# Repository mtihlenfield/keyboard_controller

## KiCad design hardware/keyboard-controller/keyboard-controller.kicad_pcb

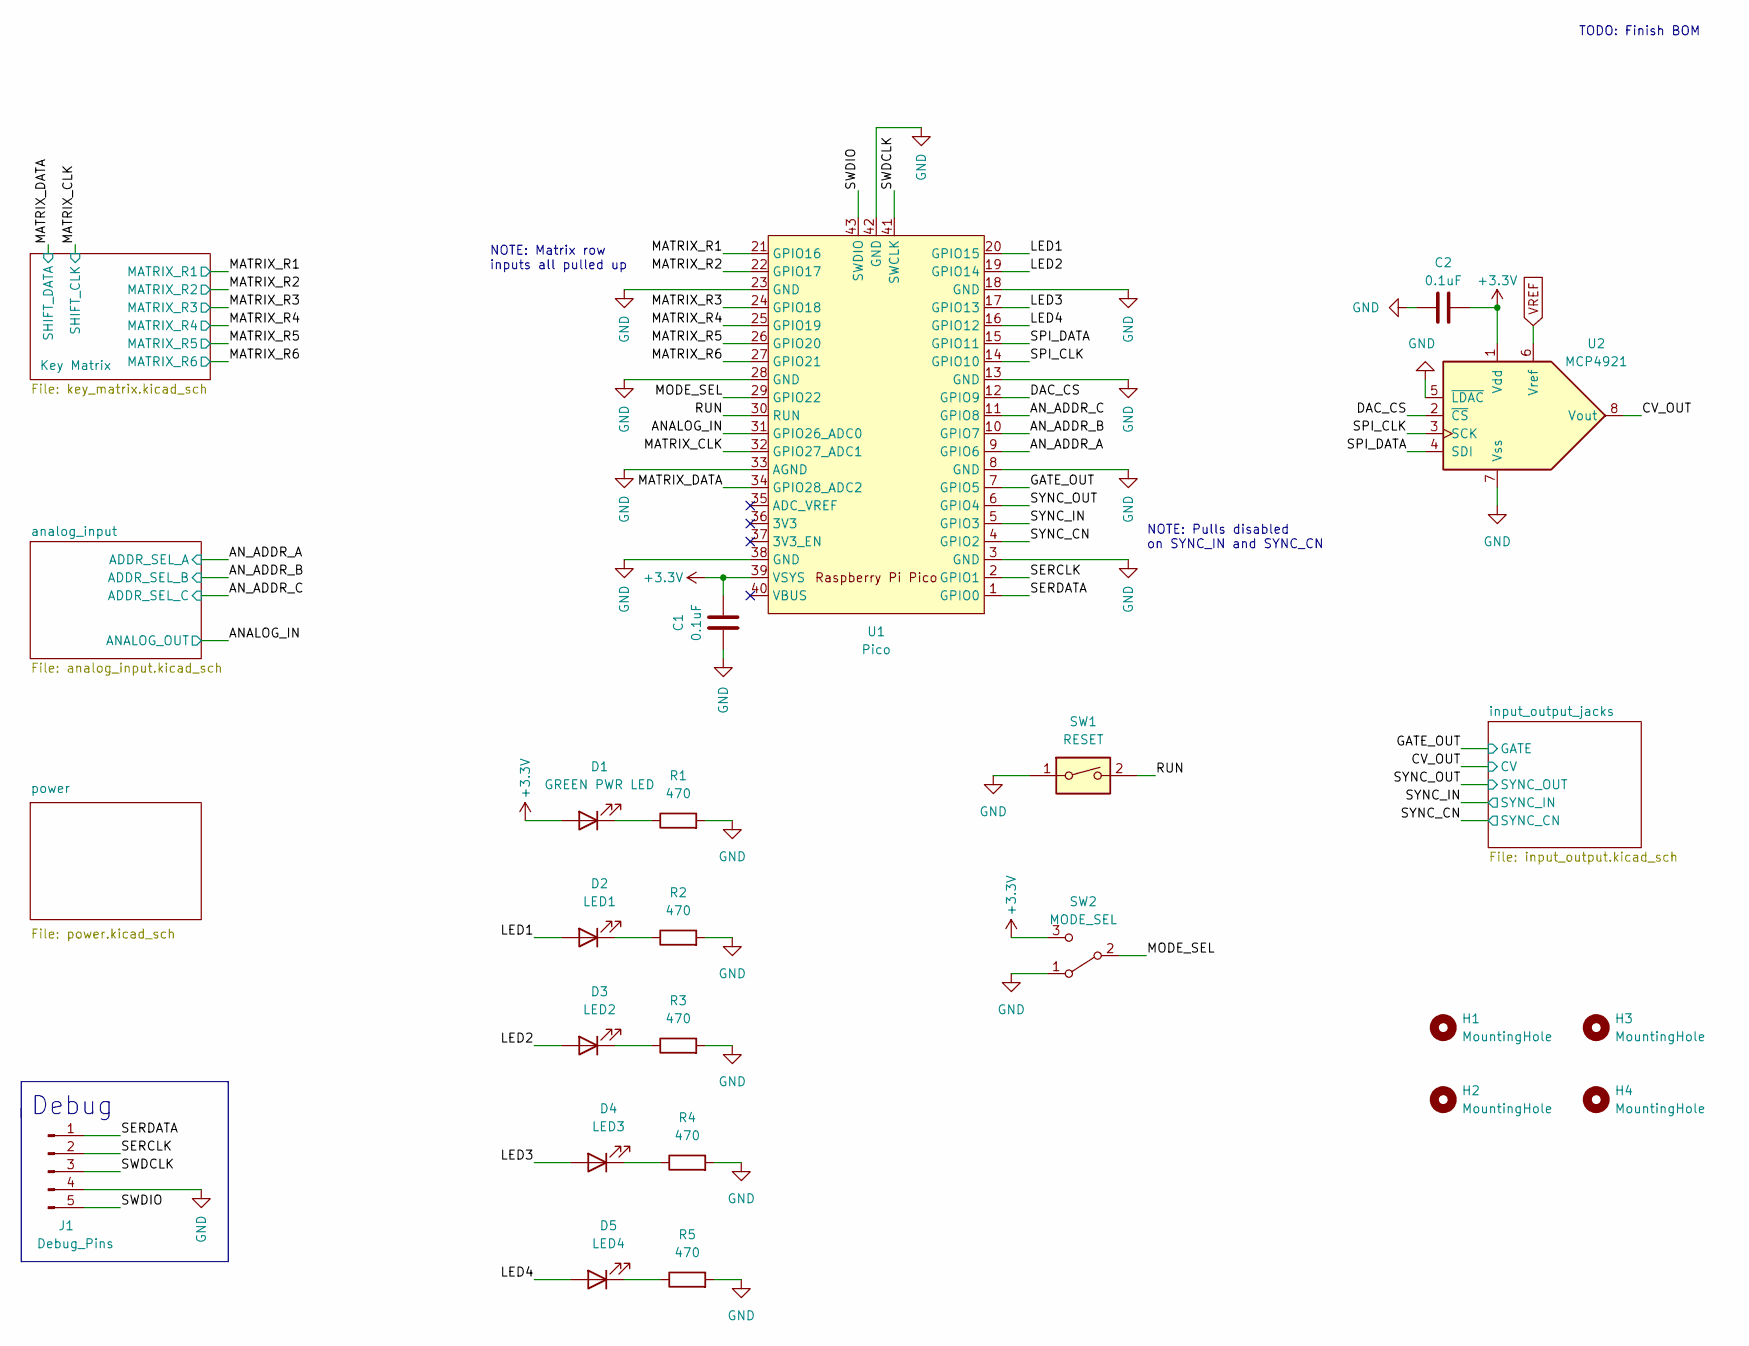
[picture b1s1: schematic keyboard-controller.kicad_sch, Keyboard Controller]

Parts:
C1, C2: 0.1uF; C_Disc_D5.0mm_W2.5mm_P3.0mm; Manufacturer Part No. 0.1uF 50V Ceramic Disc Capacitor
D1: GREEN PWR LED; LED_D5.0mm; Manufacturer Part No. LED 5mm Green
D2: LED1; LED_D5.0mm; Manufacturer Part No. C503B-RAN-CZ0C0AA1
D3: LED2; LED_D5.0mm; Manufacturer Part No. C503B-RAN-CZ0C0AA1
D4: LED3; LED_D5.0mm; Manufacturer Part No. C503B-RAN-CZ0C0AA1
D5: LED4; LED_D5.0mm; Manufacturer Part No. C503B-RAN-CZ0C0AA1
H1, H2, H3, H4: MountingHole; MountingHole_3.2mm_M3; Manufacturer Part No. N/A
J1: Debug_Pins; PinHeader_1x05_P2.54mm_Vertical; Manufacturer Part No. PHSS05G10
R1, R2, R3, R4, R5: 470; R_Axial_DIN0207_L6.8mm_D2.5mm_P10.16mm_Horizontal
SW1: RESET; SW_PUSH_6mm; Manufacturer Part No. Tact Switch 6x6mm 5mm
SW2: MODE_SEL; Slide_Switch_SPDT_SS12F44G5; Manufacturer Part No. SS12F44G5
U1: Pico; RPi_Pico_SMD_TH
U2: MCP4921; DIP-8_W7.62mm_Socket

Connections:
+3.3V: C1.2, C2.2, D1.2 (A), SW2.3 (C), U1.39 (VSYS), U2.1 (Vdd); also elsewhere on the board
/ANALOG_IN: U1.31 (GPIO26_ADC0); also elsewhere on the board
/AN_ADDR_A: U1.9 (GPIO6); also elsewhere on the board
/AN_ADDR_B: U1.10 (GPIO7); also elsewhere on the board
/AN_ADDR_C: U1.11 (GPIO8); also elsewhere on the board
/CV_OUT: U2.8 (Vout); also elsewhere on the board
/DAC_CS: U1.12 (GPIO9), U2.2 (~CS)
/GATE_OUT: U1.7 (GPIO5); also elsewhere on the board
/LED1: D2.2 (A), U1.20 (GPIO15)
/LED2: D3.2 (A), U1.19 (GPIO14)
/LED3: D4.2 (A), U1.17 (GPIO13)
/LED4: D5.2 (A), U1.16 (GPIO12)
/MATRIX_CLK: U1.32 (GPIO27_ADC1); also elsewhere on the board
/MATRIX_DATA: U1.34 (GPIO28_ADC2); also elsewhere on the board
/MATRIX_R1: U1.21 (GPIO16); also elsewhere on the board
/MATRIX_R2: U1.22 (GPIO17); also elsewhere on the board
/MATRIX_R3: U1.24 (GPIO18); also elsewhere on the board
/MATRIX_R4: U1.25 (GPIO19); also elsewhere on the board
/MATRIX_R5: U1.26 (GPIO20); also elsewhere on the board
/MATRIX_R6: U1.27 (GPIO21); also elsewhere on the board
/MODE_SEL: SW2.2 (B), U1.29 (GPIO22)
/RUN: SW1.2, U1.30 (RUN)
/SERCLK: J1.2, U1.2 (GPIO1)
/SERDATA: J1.1, U1.1 (GPIO0)
/SPI_CLK: U1.14 (GPIO10), U2.3 (SCK)
/SPI_DATA: U1.15 (GPIO11), U2.4 (SDI)
/SWDCLK: J1.3, U1.41 (SWCLK)
/SWDIO: J1.5, U1.43 (SWDIO)
/SYNC_CN: U1.4 (GPIO2); also elsewhere on the board
/SYNC_IN: U1.5 (GPIO3); also elsewhere on the board
/SYNC_OUT: U1.6 (GPIO4); also elsewhere on the board
GND: C1.1, C2.1, J1.4, R1.2, R2.2, R3.2, R4.2, R5.2, SW1.1, SW2.1 (A), U1.3 (GND), U1.8 (GND), U1.13 (GND), U1.18 (GND), U1.23 (GND), U1.28 (GND), U1.33 (AGND), U1.38 (GND), U1.42 (GND), U2.5 (~LDAC), U2.7 (Vss); also elsewhere on the board
unnamed: D1.1 (K), R1.1
unnamed: D2.1 (K), R2.1
unnamed: D3.1 (K), R3.1
unnamed: D4.1 (K), R4.1
unnamed: D5.1 (K), R5.1
VREF: U2.6 (Vref); also elsewhere on the board

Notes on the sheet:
NOTE: Matrix row inputs all pulled up
TODO: Finish BOM
NOTE: Pulls disabled on SYNC_IN and SYNC_CN
Debug

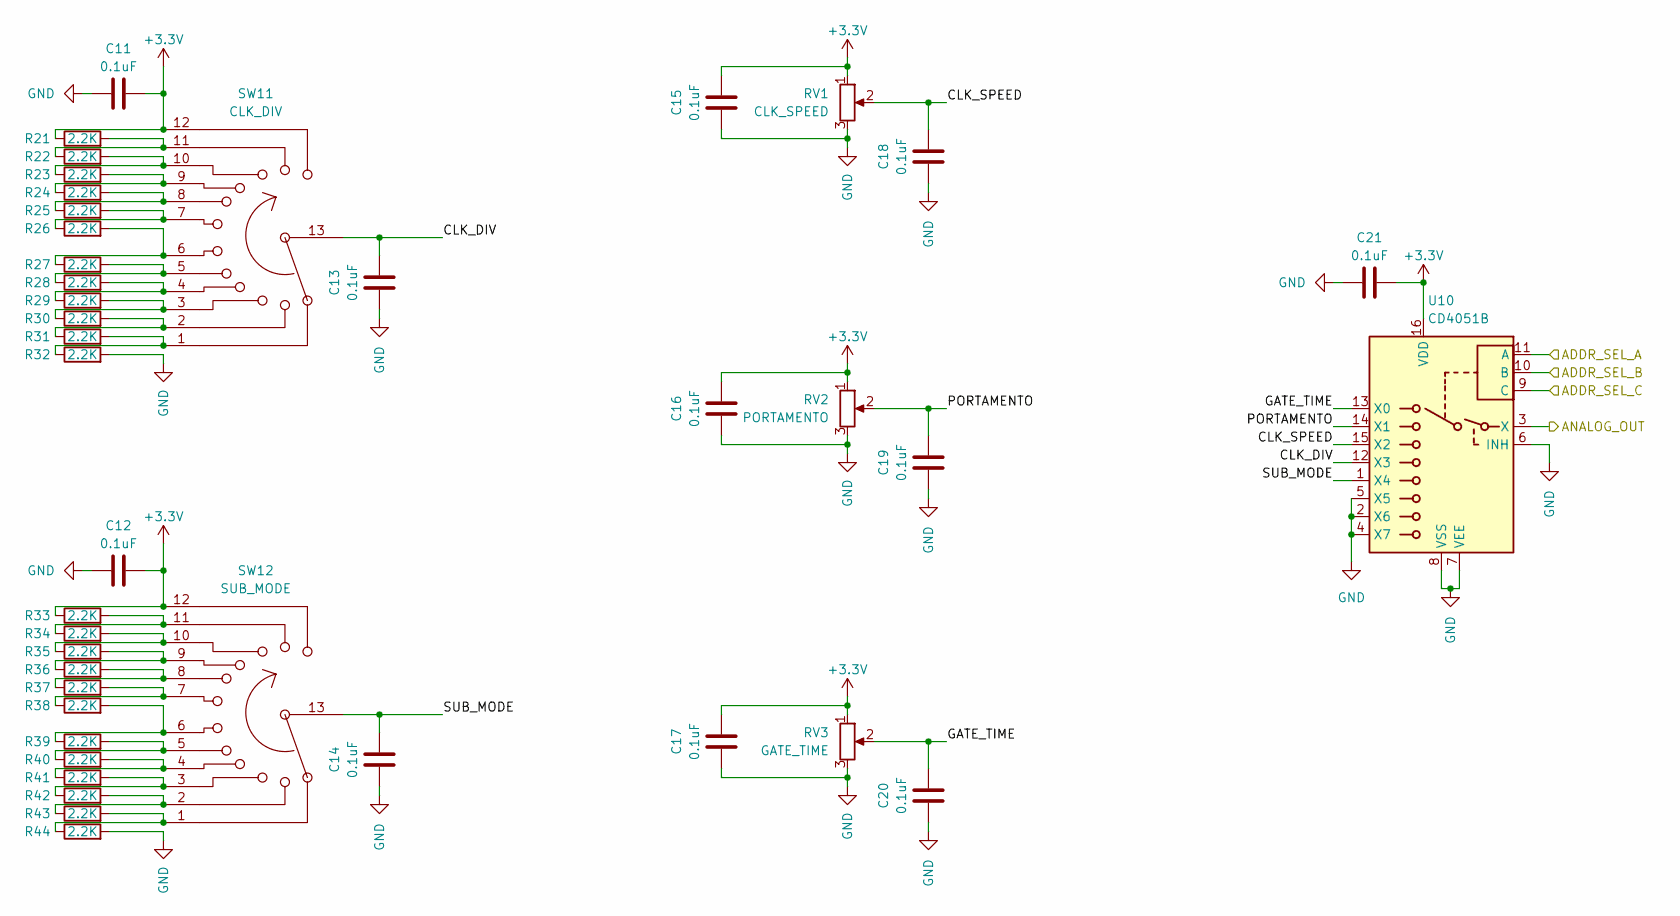
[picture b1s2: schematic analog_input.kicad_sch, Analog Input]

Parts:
C11, C12, C13, C14, C15, C16, C17, C18, C19, C20, C21: 0.1uF; C_Disc_D5.0mm_W2.5mm_P3.0mm; Manufacturer Part No. 0.1uF 50V Ceramic Disc Capacitor
R21, R22, R23, R24, R25, R26, R27, R28, R29, R30, R31, R32, R33, R34, R35, R36, R37, R38, R39, R40, R41, R42, R43, R44: 2.2K; R_Axial_DIN0207_L6.8mm_D2.5mm_P10.16mm_Horizontal
RV1: CLK_SPEED; Potentiometer_Alpha_RV09AF-40-20K-B1K_Single_Vertical
RV2: PORTAMENTO; Potentiometer_Alpha_RV09AF-40-20K-B1K_Single_Vertical
RV3: GATE_TIME; Potentiometer_Alpha_RV09AF-40-20K-B1K_Single_Vertical
SW11: CLK_DIV; Clock_Div_Switch
SW12: SUB_MODE; Sub_Mode_Switch
U10: CD4051B; DIP-16_W7.62mm_Socket

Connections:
+3.3V: C11.2, C12.2, C15.2, C16.2, C17.2, C21.2, R21.1, R33.1, RV1.1, RV2.1, RV3.1, SW11.12, SW12.12, U10.16 (VDD); also elsewhere on the board
/ANALOG_IN: U10.3 (X); also elsewhere on the board
/AN_ADDR_A: U10.11 (A); also elsewhere on the board
/AN_ADDR_B: U10.10 (B); also elsewhere on the board
/AN_ADDR_C: U10.9 (C); also elsewhere on the board
/analog_input/CLK_DIV: C13.2, SW11.13, U10.12 (X3)
/analog_input/CLK_SPEED: C18.2, RV1.2, U10.15 (X2)
/analog_input/GATE_TIME: C20.2, RV3.2, U10.13 (X0)
/analog_input/PORTAMENTO: C19.2, RV2.2, U10.14 (X1)
/analog_input/SUB_MODE: C14.2, SW12.13, U10.1 (X4)
GND: C11.1, C12.1, C13.1, C14.1, C15.1, C16.1, C17.1, C18.1, C19.1, C20.1, C21.1, R32.2, R44.2, RV1.3, RV2.3, RV3.3, U10.2 (X6), U10.4 (X7), U10.5 (X5), U10.6 (INH), U10.7 (VEE), U10.8 (VSS); also elsewhere on the board
unnamed: R21.2, R22.1, SW11.11
unnamed: R22.2, R23.1, SW11.10
unnamed: R23.2, R24.1, SW11.9
unnamed: R24.2, R25.1, SW11.8
unnamed: R25.2, R26.1, SW11.7
unnamed: R26.2, R27.1, SW11.6
unnamed: R27.2, R28.1, SW11.5
unnamed: R28.2, R29.1, SW11.4
unnamed: R29.2, R30.1, SW11.3
unnamed: R30.2, R31.1, SW11.2
unnamed: R31.2, R32.1, SW11.1
unnamed: R33.2, R34.1, SW12.11
unnamed: R34.2, R35.1, SW12.10
unnamed: R35.2, R36.1, SW12.9
unnamed: R36.2, R37.1, SW12.8
unnamed: R37.2, R38.1, SW12.7
unnamed: R38.2, R39.1, SW12.6
unnamed: R39.2, R40.1, SW12.5
unnamed: R40.2, R41.1, SW12.4
unnamed: R41.2, R42.1, SW12.3
unnamed: R42.2, R43.1, SW12.2
unnamed: R43.2, R44.1, SW12.1

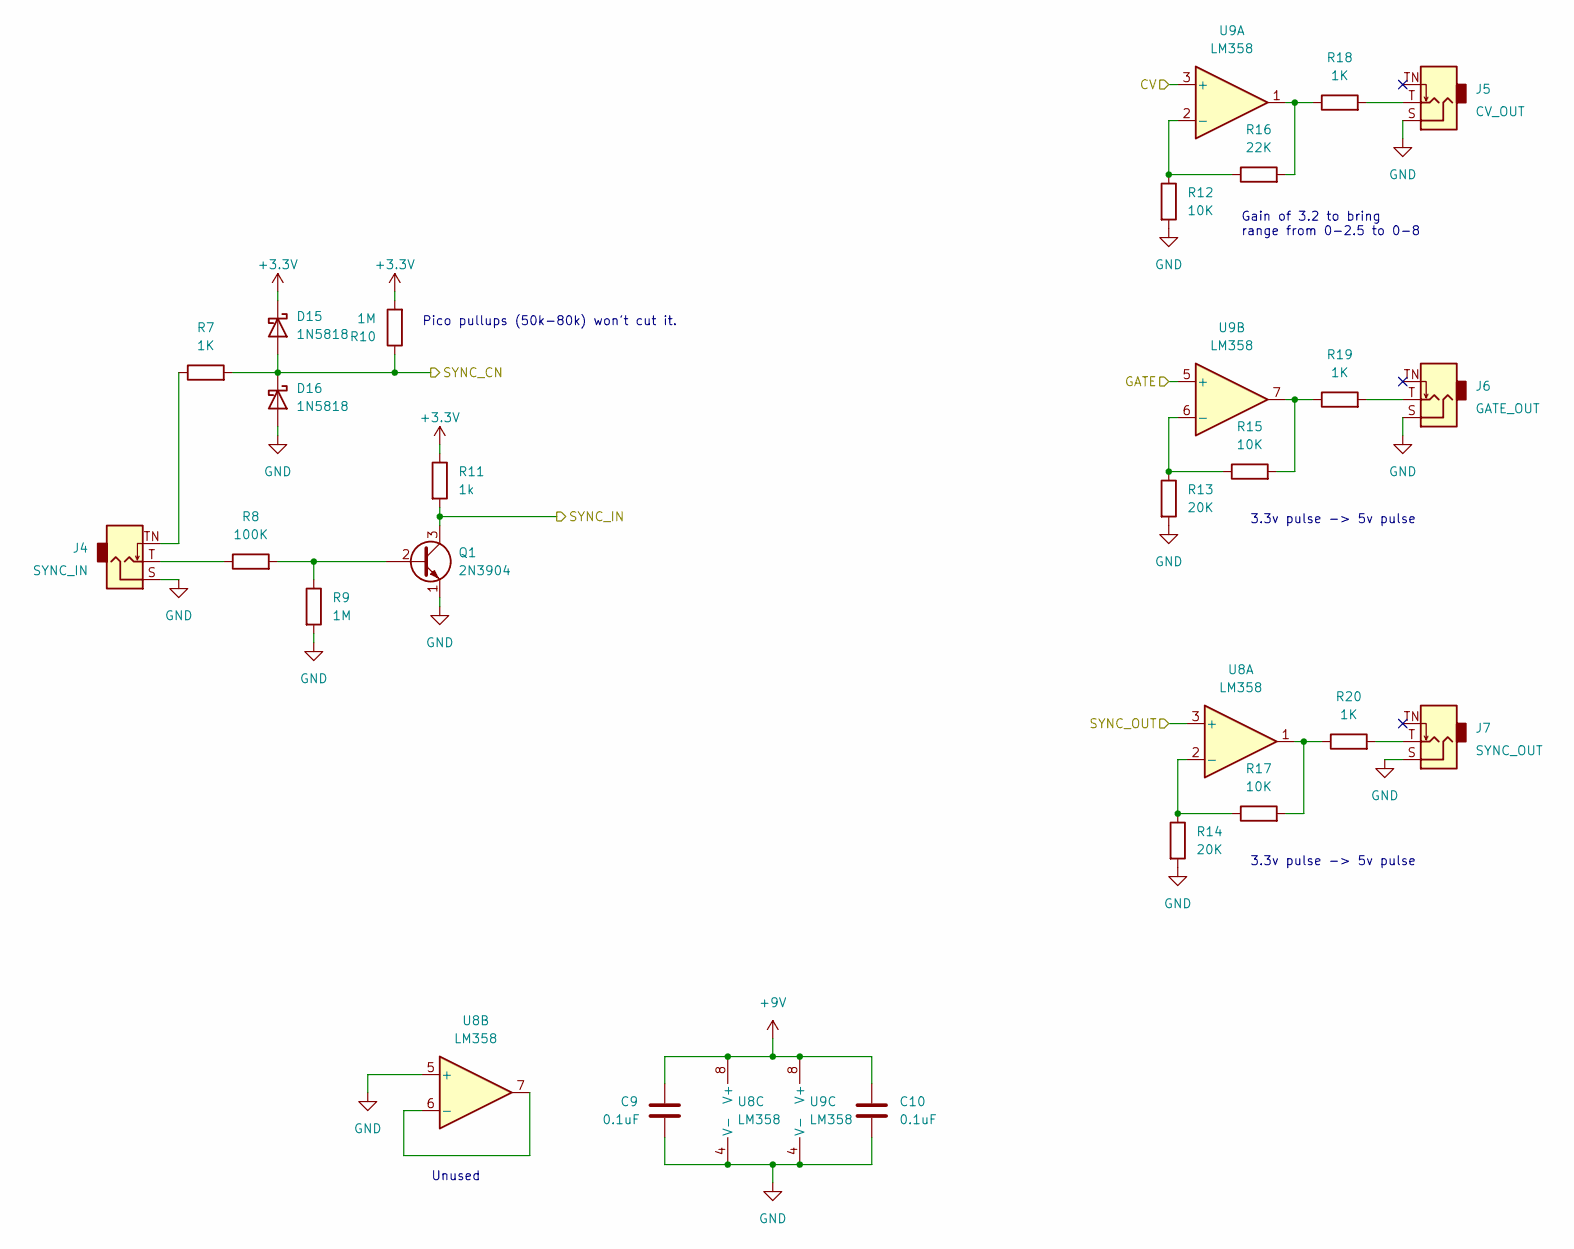
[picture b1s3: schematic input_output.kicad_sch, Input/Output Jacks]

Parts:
C9, C10: 0.1uF; C_Disc_D5.0mm_W2.5mm_P3.0mm; Manufacturer Part No. 0.1uF 50V Ceramic Disc Capacitor
D15, D16: 1N5818; D_DO-41_SOD81_P10.16mm_Horizontal; Manufacturer Part No. 1N5818
J4: SYNC_IN; Jack_3.5mm_QingPu_WQP-PJ398SM_Vertical; Manufacturer Part No. PJ-629HAN-05
J5: CV_OUT; Jack_3.5mm_QingPu_WQP-PJ398SM_Vertical; Manufacturer Part No. PJ-629HAN-05
J6: GATE_OUT; Jack_3.5mm_QingPu_WQP-PJ398SM_Vertical; Manufacturer Part No. PJ-629HAN-05
J7: SYNC_OUT; Jack_3.5mm_QingPu_WQP-PJ398SM_Vertical; Manufacturer Part No. PJ-629HAN-05
Q1: 2N3904; TO-92_Inline; Manufacturer Part No. 2N3904
R7, R18, R19, R20: 1K; R_Axial_DIN0207_L6.8mm_D2.5mm_P10.16mm_Horizontal
R8: 100K; R_Axial_DIN0207_L6.8mm_D2.5mm_P10.16mm_Horizontal
R9, R10: 1M; R_Axial_DIN0207_L6.8mm_D2.5mm_P10.16mm_Horizontal
R11: 1k; R_Axial_DIN0207_L6.8mm_D2.5mm_P10.16mm_Horizontal
R12, R15, R17: 10K; R_Axial_DIN0207_L6.8mm_D2.5mm_P10.16mm_Horizontal
R13, R14: 20K; R_Axial_DIN0207_L6.8mm_D2.5mm_P10.16mm_Horizontal
R16: 22K; R_Axial_DIN0207_L6.8mm_D2.5mm_P10.16mm_Horizontal
U8, U9: LM358; DIP-8_W7.62mm_Socket

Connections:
+3.3V: D15.1 (K), R10.2, R11.1; also elsewhere on the board
+9V: C9.1, C10.1, U8.8 (V+), U9.8 (V+); also elsewhere on the board
/CV_OUT: U9.3 (+); also elsewhere on the board
/GATE_OUT: U9.5 (+); also elsewhere on the board
/SYNC_CN: D15.2 (A), D16.1 (K), R7.2, R10.1; also elsewhere on the board
/SYNC_IN: Q1.3 (C), R11.2; also elsewhere on the board
/SYNC_OUT: U8.3 (+); also elsewhere on the board
GND: C9.2, C10.2, D16.2 (A), J4.S, J5.S, J6.S, J7.S, Q1.1 (E), R9.2, R12.2, R13.2, R14.2, U8.4 (V-), U8.5 (+), U9.4 (V-); also elsewhere on the board
unnamed: J4.T, R8.1
unnamed: J4.TN, R7.1
unnamed: J5.T, R18.2
unnamed: J6.T, R19.2
unnamed: J7.T, R20.2
unnamed: Q1.2 (B), R8.2, R9.1
unnamed: R12.1, R16.1, U9.2 (-)
unnamed: R13.1, R15.1, U9.6 (-)
unnamed: R14.1, R17.1, U8.2 (-)
unnamed: R15.2, R19.1, U9.7
unnamed: R16.2, R18.1, U9.1
unnamed: R17.2, R20.1, U8.1
unnamed: U8.6 (-), U8.7

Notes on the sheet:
Pico pullups (50k-80k) won't cut it.
3.3v pulse -> 5v pulse
Unused
Gain of 3.2 to bring range from 0-2.5 to 0-8

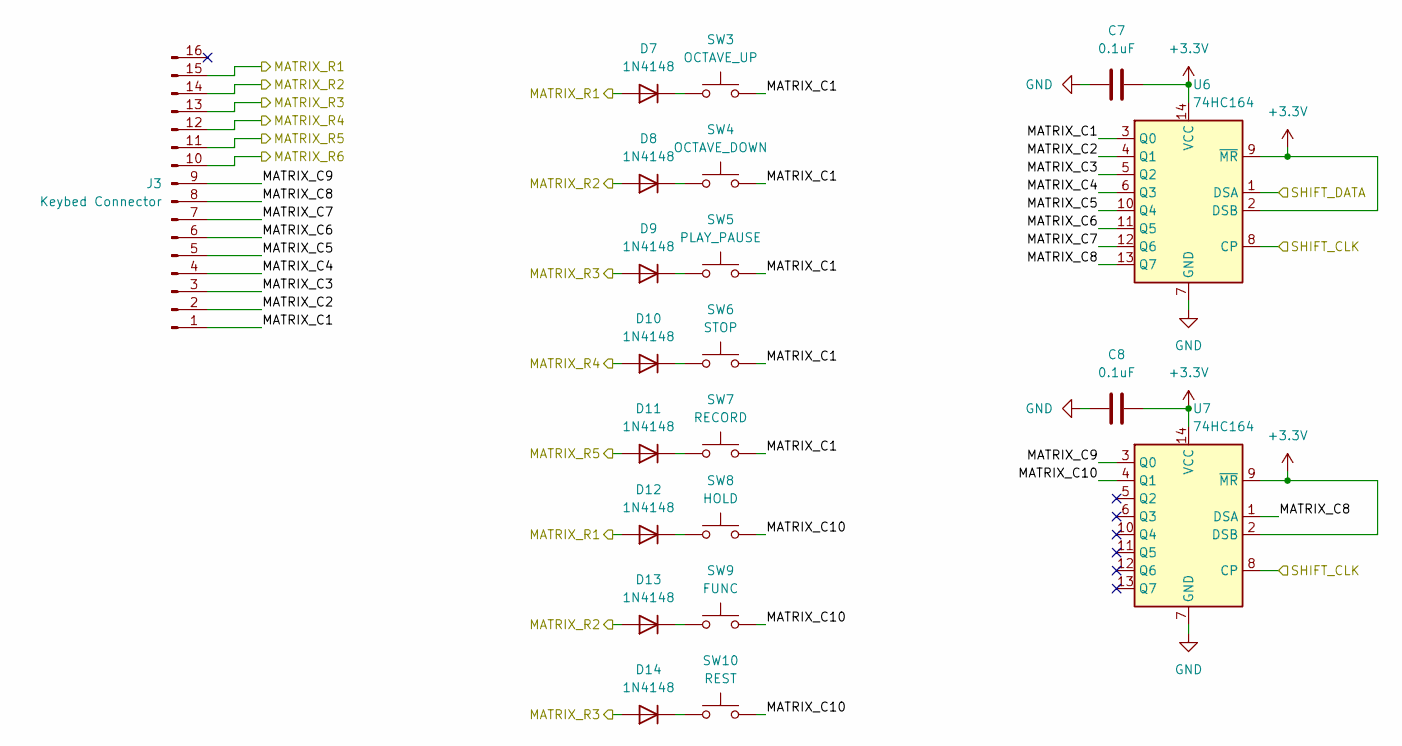
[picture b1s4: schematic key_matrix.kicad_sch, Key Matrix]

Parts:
C7, C8: 0.1uF; C_Disc_D5.0mm_W2.5mm_P3.0mm; Manufacturer Part No. 0.1uF 50V Ceramic Disc Capacitor
D7, D8, D9, D10, D11, D12, D13, D14: 1N4148; D_DO-35_SOD27_P7.62mm_Horizontal; Manufacturer Part No. 1N4148
J3: Keybed Connector; IDC-Header_2x08_P2.54mm_Vertical; Manufacturer Part No. BHD16PHZT
SW3: OCTAVE_UP; SW_PUSH_6mm; Manufacturer Part No. Tact Switch 6x6mm 5mm
SW4: OCTAVE_DOWN; SW_PUSH_6mm; Manufacturer Part No. Tact Switch 6x6mm 5mm
SW5: PLAY_PAUSE; SW_PUSH_6mm; Manufacturer Part No. Tact Switch 6x6mm 5mm
SW6: STOP; SW_PUSH_6mm; Manufacturer Part No. Tact Switch 6x6mm 5mm
SW7: RECORD; SW_PUSH_6mm; Manufacturer Part No. Tact Switch 6x6mm 5mm
SW8: HOLD; SW_PUSH_6mm; Manufacturer Part No. Tact Switch 6x6mm 5mm
SW9: FUNC; SW_PUSH_6mm; Manufacturer Part No. Tact Switch 6x6mm 5mm
SW10: REST; SW_PUSH_6mm; Manufacturer Part No. Tact Switch 6x6mm 5mm
U6, U7: 74HC164; DIP-14_W7.62mm_Socket

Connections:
+3.3V: C7.2, C8.2, U6.2 (DSB), U6.9 (~MR), U6.14 (VCC), U7.2 (DSB), U7.9 (~MR), U7.14 (VCC); also elsewhere on the board
/Key Matrix/MATRIX_C1: J3.1, SW3.2, SW4.2, SW5.2, SW6.2, SW7.2, U6.3 (Q0)
/Key Matrix/MATRIX_C2: J3.2, U6.4 (Q1)
/Key Matrix/MATRIX_C3: J3.3, U6.5 (Q2)
/Key Matrix/MATRIX_C4: J3.4, U6.6 (Q3)
/Key Matrix/MATRIX_C5: J3.5, U6.10 (Q4)
/Key Matrix/MATRIX_C6: J3.6, U6.11 (Q5)
/Key Matrix/MATRIX_C7: J3.7, U6.12 (Q6)
/Key Matrix/MATRIX_C8: J3.8, U6.13 (Q7), U7.1 (DSA)
/Key Matrix/MATRIX_C9: J3.9, U7.3 (Q0)
/Key Matrix/MATRIX_C10: SW8.2, SW9.2, SW10.2, U7.4 (Q1)
/MATRIX_CLK: U6.8 (CP), U7.8 (CP); also elsewhere on the board
/MATRIX_DATA: U6.1 (DSA); also elsewhere on the board
/MATRIX_R1: D7.2 (A), D12.2 (A), J3.15; also elsewhere on the board
/MATRIX_R2: D8.2 (A), D13.2 (A), J3.14; also elsewhere on the board
/MATRIX_R3: D9.2 (A), D14.2 (A), J3.13; also elsewhere on the board
/MATRIX_R4: D10.2 (A), J3.12; also elsewhere on the board
/MATRIX_R5: D11.2 (A), J3.11; also elsewhere on the board
/MATRIX_R6: J3.10; also elsewhere on the board
GND: C7.1, C8.1, U6.7 (GND), U7.7 (GND); also elsewhere on the board
unnamed: D7.1 (K), SW3.1
unnamed: D8.1 (K), SW4.1
unnamed: D9.1 (K), SW5.1
unnamed: D10.1 (K), SW6.1
unnamed: D11.1 (K), SW7.1
unnamed: D12.1 (K), SW8.1
unnamed: D13.1 (K), SW9.1
unnamed: D14.1 (K), SW10.1

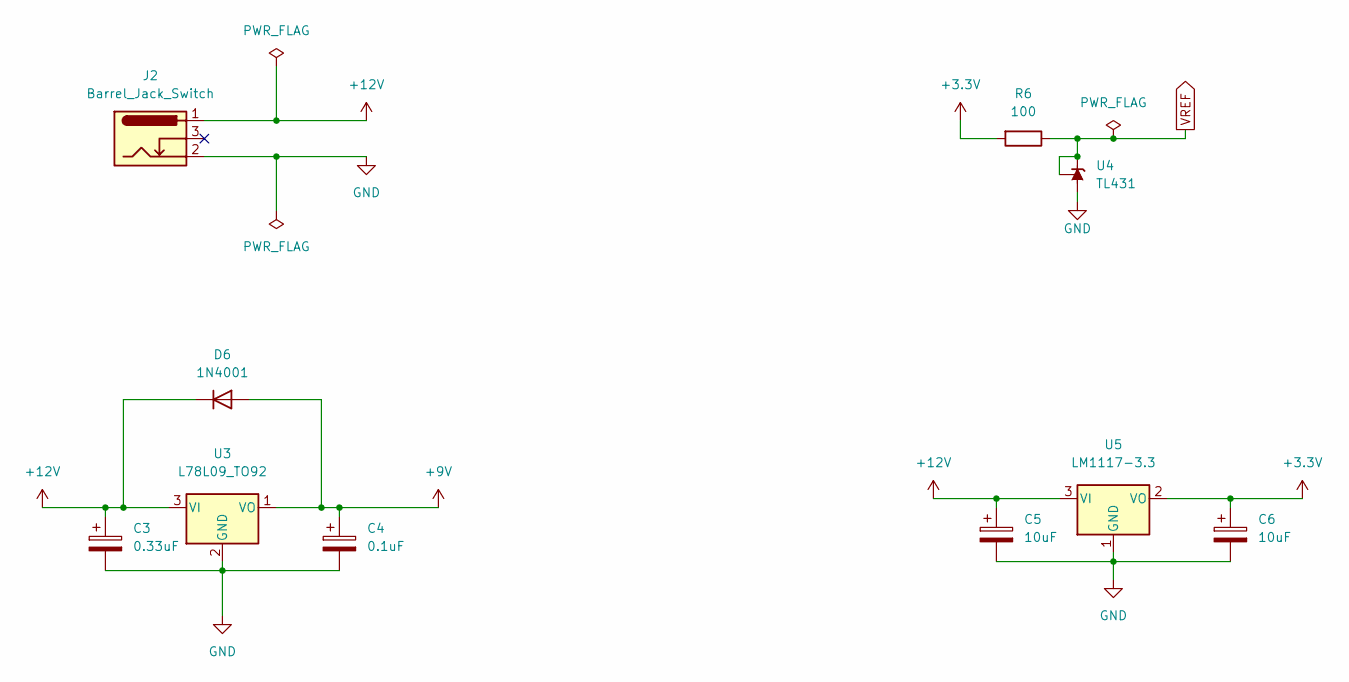
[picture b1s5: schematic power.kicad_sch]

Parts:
C3: 0.33uF; CP_Radial_Tantal_D4.5mm_P2.50mm; Manufacturer Part No. 0.33uF 35V Radial Capacitor Tantalum
C4: 0.1uF; CP_Radial_Tantal_D4.5mm_P2.50mm; Manufacturer Part No. 0.1uF 35V Radial Capacitor Tantalum
C5, C6: 10uF; CP_Radial_Tantal_D4.5mm_P2.50mm; Manufacturer Part No. 10uF 35V Radial Capacitor Tantalum
D6: 1N4001; D_DO-41_SOD81_P10.16mm_Horizontal; Manufacturer Part No. 1N4001
J2: Barrel_Jack_Switch; BarrelJack_Horizontal_2.1mm_WEALTH_METAL; Manufacturer Part No. DC Power Jack 2.1mm
R6: 100; R_Axial_DIN0207_L6.8mm_D2.5mm_P10.16mm_Horizontal
U3: L78L09_TO92; TO-92_Inline
U4: TL431; TO-92_Inline; Manufacturer Part No. TL431ACL
U5: LM1117-3.3; TO-220-3_Horizontal_TabDown

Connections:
+3.3V: C6.1, R6.2, U5.2 (VO); also elsewhere on the board
+9V: C4.1, D6.2 (A), U3.1 (VO); also elsewhere on the board
+12V: C3.1, C5.1, D6.1 (K), J2.1, U3.3 (VI), U5.3 (VI)
GND: C3.2, C4.2, C5.2, C6.2, J2.2, U3.2 (GND), U4.2 (A), U5.1 (GND); also elsewhere on the board
VREF: R6.1, U4.1 (REF), U4.3 (K); also elsewhere on the board

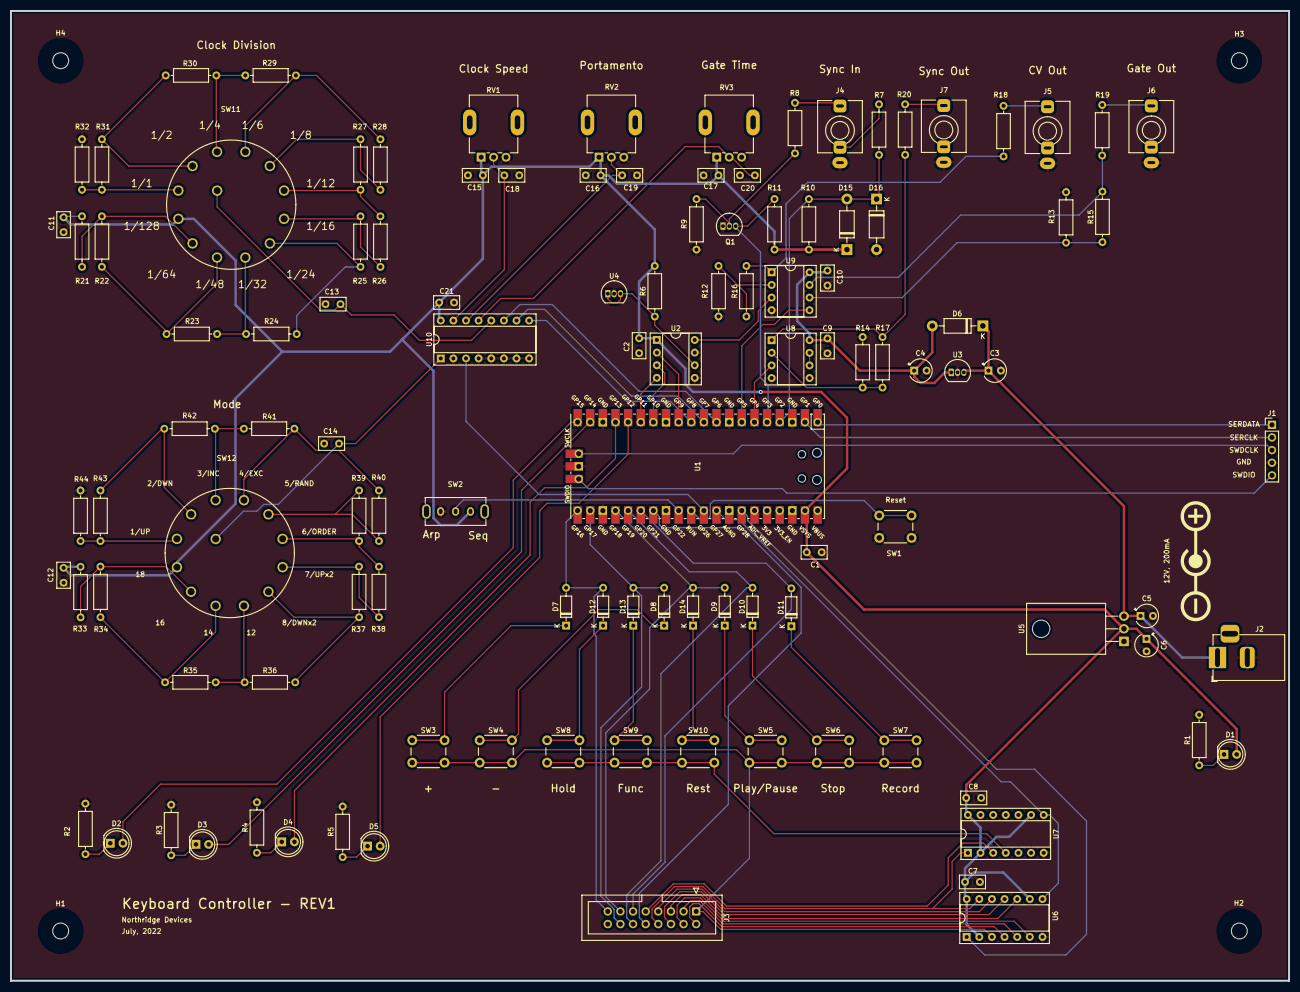
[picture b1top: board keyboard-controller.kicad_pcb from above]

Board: 2 copper layers, 257.0 x 195.0 mm, 118 parts (0 on the bottom side), 98 nets.

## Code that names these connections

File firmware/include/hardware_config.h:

#ifndef __HARDWARE_CONFIG_H__
#define __HARDWARE_CONFIG_H__

#define DAC_SPI_PORT spi1
#define DAC_PIN_CS 13 // GP13
#define DAC_PIN_SCK 10 // GP10
#define DAC_PIN_MOSI 11 // GP11
#define DAC_REFV 2.5 // Using a TL431 in it's default state
#define DAC_CLK_SPEED (1000 * 1000) // 1Mhz

// Amount of gain applied to the CV signal by our op-amp
// configuration.
#define CV_OPAMP_GAIN 3.2

#define GATE_OUT_PIN 5 // GP5

#define LED_PIN 25 // GP25

#define SHIFT_REG_CLK_PIN 14 // GP14
#define SHIFT_REG_DATA_PIN 15 // GP15

// Total number of shift register outputs
#define SHIFT_REG_OUTPUTS 16

// NOTE rows are held high,
#define MATRIX_ROWS 6
#define MATRIX_COLS 10
#define NUM_MATRIX_KEYS (MATRIX_ROWS * MATRIX_COLS)

#define MODEL_SEL_PIN 22 // GP22

#define ANALOG_IN_PIN 26 // GP26
#define ANALOG_IN_CHANNEL 0

#define AN_ADDR_A_PIN 6 // GP6
#define AN_ADDR_B_PIN 7 // GP7
#define AN_ADDR_C_PIN 8 // GP8

#define NUM_ANALOG_INPUTS 5

#define ANALOG_ADDR_MASK (7 << 6)
#define MASK_CLK_SPEED 0
#define MASK_PORTAMENTO (1 << 6)
#define MASK_GATE_TIME (2 << 6)
#define MASK_CLK_DIV (3 << 6)
#define MASK_SUB_MODE (4 << 6)
#define MASK_GND (5 << 6)

#endif

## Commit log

2022-03-31 Added initial key matrix code and cleaned up repo
2022-03-31 Removed unused #defines from keyboard.c
2022-03-31 Added voltage regulators and power input to schematic
2022-03-31 Reorganized hardware folder to keep libraries locally. Added footprints to most symbols
2022-03-31 Removed pico-sdk
2022-03-31 Fixed pico-sdk submodule
2022-04-01 Added cv/gate output jacks
2022-04-04 Schematic updates: Added filter caps on all ICs, resolved some TODOs
2022-04-06 Fixed shift register <-> pico pins in schematic. Moved shift register clk/data pins
2022-04-10 Implemented main keyboard functionality
2022-04-11 Set gate low on startup. Linting
2022-04-11 Minor comment cleanup
2022-04-12 Code cleanup. Switched keyboard connector to 16pin IDC
2022-04-12 Added datasheets to docs
2022-04-14 Added more docs
2022-04-18 Switched over to using queues/polling rather than fifo/irq
2022-04-19 Reworked matrix scanning to use a timer rather than a scanning loop.
2022-04-19 Added octave shift buttons
2022-04-26 Tidied schematic
2022-05-27 Added more IO
2022-05-28 Added hardware_config.h and updated pin configuration
2022-05-28 Changed 'km' code to be 'io'. Started adding plumbing for additional io events
2022-05-28 Added filter caps on pots and rotary switches
2022-05-29 Added analog switch for analog input
2022-06-02 Added start of analog input handling
2022-06-18 Added footprint for rotary switches
2022-06-19 Updated hardware_config and fixed sync_cn
2022-06-27 Completed schematic rev1. Started placing pcb
2022-07-17 Completed initial pcb design
2022-07-23 Converted PCB to 2-layer
2022-07-23 Added more text detail to PCB. Completed more of BOM
2022-07-23 Cleaned up tracks
2022-07-23 Completed BOM
